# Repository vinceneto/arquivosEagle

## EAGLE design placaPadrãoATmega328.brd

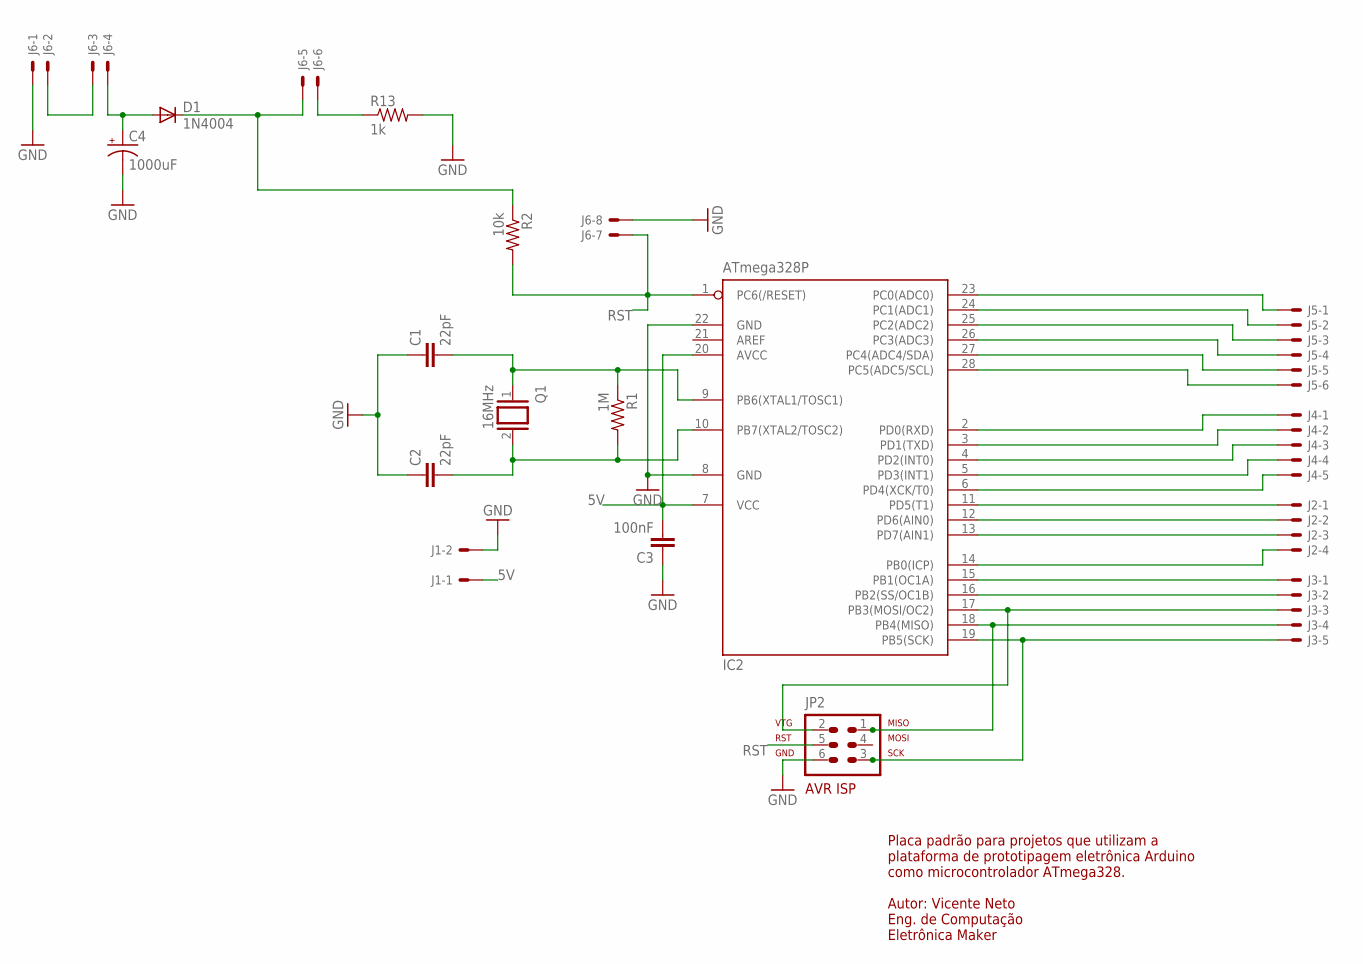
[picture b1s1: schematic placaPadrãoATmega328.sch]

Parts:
C1, C2: 22pF; C025-025X050
C3: 100nF; C025-025X050
C4: 1000uF; E5-10,5
D1: 1N4004; DO41-10
IC2: ATmega328P; DIL28-3
J1: 22-27-2021-02; 6410-02
J2: 22-27-2041-04; 6410-04
J3, J4: 22-27-2051-05; 6410-05
J5: 22-27-2061-06; 6410-06
J6: 22-27-2081-08; 6410-08
JP2: ICSP; AVR-ISP-6
Q1: 16MHz; QS
R1: 1M; 0204/7
R2: 10k; 0204/7
R13: 1k; 0204/7

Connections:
5V: C3.2, D1.C, IC2.7 (VCC), IC2.20 (AVCC), J1.1, J6.5, R2.1
A0: IC2.23 (PC0(ADC0)), J5.1
A1: IC2.24 (PC1(ADC1)), J5.2
A2: IC2.25 (PC2(ADC2)), J5.3
A3: IC2.26 (PC3(ADC3)), J5.4
A4: IC2.27 (PC4(ADC4/SDA)), J5.5
A5: IC2.28 (PC5(ADC5/SCL)), J5.6
GND: C1.1, C2.1, C3.1, C4.-, IC2.8 (GND), IC2.22 (GND), J1.2, J6.1, J6.8, JP2.6, R13.2
unnamed: C1.2, IC2.9 (PB6(XTAL1/TOSC1)), Q1.1, R1.1
unnamed: C2.2, IC2.10 (PB7(XTAL2/TOSC2)), Q1.2, R1.2
unnamed: IC2.19 (PB5(SCK)), J3.5, JP2.3
unnamed: C4.+, D1.A, J6.4
unnamed: IC2.3 (PD1(TXD)), J4.2
unnamed: IC2.18 (PB4(MISO)), J3.4, JP2.1
unnamed: IC2.17 (PB3(MOSI/OC2)), J3.3, JP2.2
unnamed: IC2.2 (PD0(RXD)), J4.1
unnamed: IC2.4 (PD2(INT0)), J4.3
unnamed: IC2.5 (PD3(INT1)), J4.4
unnamed: IC2.6 (PD4(XCK/T0)), J4.5
unnamed: IC2.11 (PD5(T1)), J2.1
unnamed: IC2.12 (PD6(AIN0)), J2.2
unnamed: IC2.13 (PD7(AIN1)), J2.3
unnamed: IC2.14 (PB0(ICP)), J2.4
unnamed: IC2.15 (PB1(OC1A)), J3.1
unnamed: IC2.16 (PB2(SS/OC1B)), J3.2
unnamed: J6.2, J6.3
unnamed: J6.6, R13.1
RST: IC2.1 (PC6(/RESET)), J6.7, JP2.5, R2.2

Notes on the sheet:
Placa padrão para projetos que utilizam a plataforma de prototipagem eletrônica Arduino como microcontrolador ATmega328. Autor: Vicente Neto Eng. de Computação Eletrônica Maker

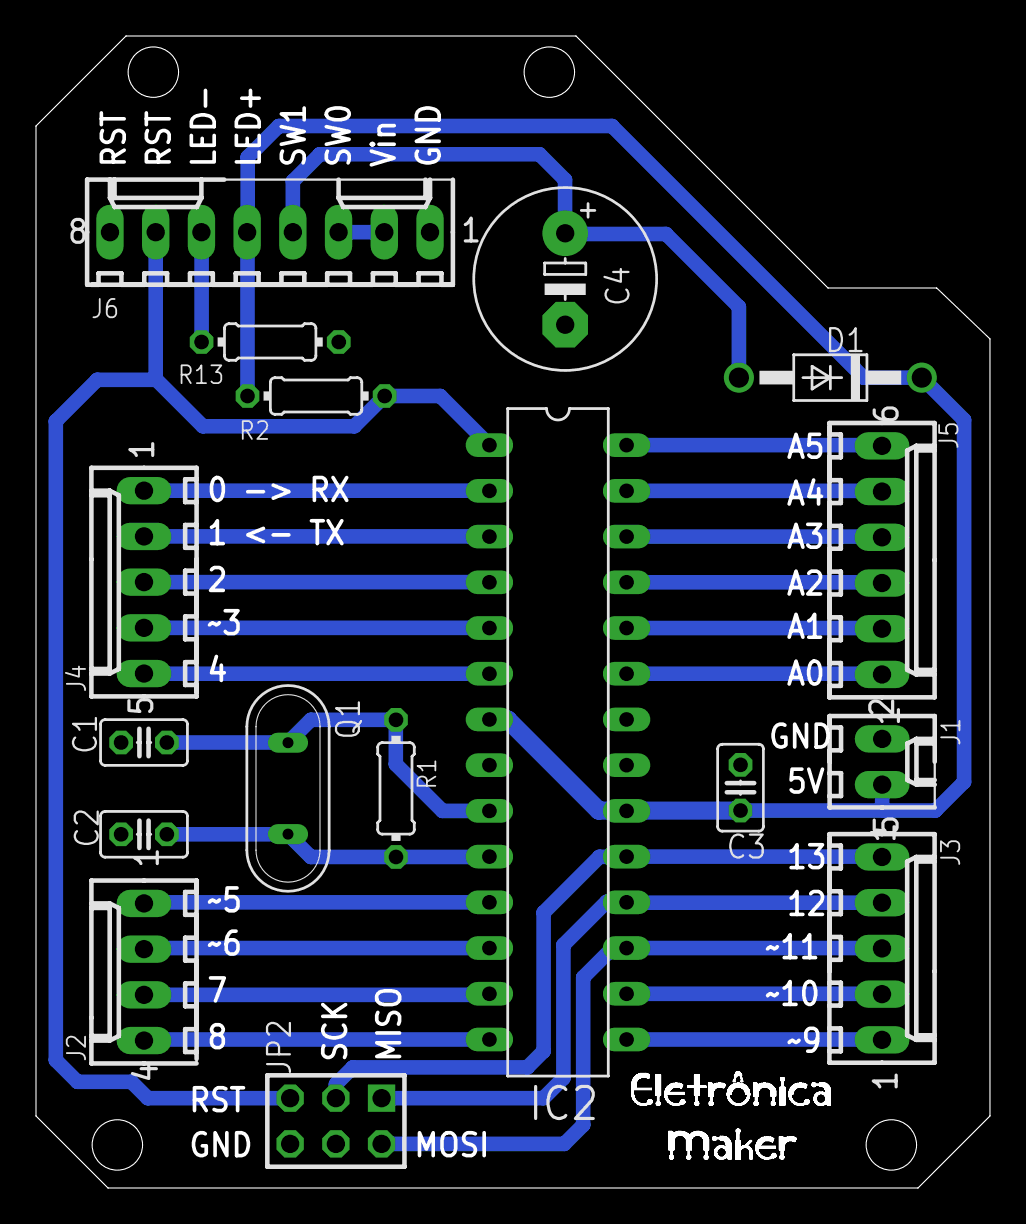
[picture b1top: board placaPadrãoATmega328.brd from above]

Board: 2 copper layers, 53.0 x 64.0 mm, 17 parts (0 on the bottom side), 28 nets.

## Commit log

2018-03-29 arquivosEagle
    Arquivos .brd e .sch
